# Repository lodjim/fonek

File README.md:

# fonek

Track your own things through Apple's Find My network and see them on your own map, with
hardware you can build yourself.

fonek is three parts that work together:

- **A tag** ([`fonek/`](fonek/README.md)): an open KiCad design for a rechargeable ESP32 BLE
  tag with USB-C charging, plus the [firmware instructions](firmware/README.md) to turn any
  ESP32 dev board into a beacon.
- **A backend** ([`backend/`](backend/)): a FastAPI service that fetches the encrypted
  location reports from Apple with [FindMy.py](https://github.com/malmeloo/FindMy.py),
  decrypts them with the tag's private key and stores them in SQLite. No Mac required.
- **A web app** ([`web/`](web/)): a Next.js + Leaflet dashboard showing each tag's latest
  position and history.

> **Status: prototype.** The software runs today with an ESP32 dev board. The rev A PCB
> passes KiCad ERC/DRC but has not been built and tested yet; see its
> [release checks](fonek/docs/verification.md). fonek is not an Apple-certified Find My
> accessory and relies on an unofficial Apple API.

## How it works

```mermaid
flowchart LR
  TAG["Tag<br>ESP32 + OpenHaystack firmware"] -- "BLE advertisement<br>(public key)" --> PHONE[Nearby iPhones]
  PHONE -- "encrypted location report" --> APPLE[(Apple Find My)]
  APPLE -- "reports for our keys" --> BACKEND["backend<br>FastAPI + FindMy.py"]
  BACKEND --> DB[(data/fonek.db)]
  WEB["web<br>Next.js + Leaflet"] -- "/api" --> BACKEND
```

Each tag has a key pair. The tag broadcasts the public key over Bluetooth. Any iPhone that
passes by encrypts its own location with that key and uploads it to Apple. Only the holder
of the private key can decrypt the report, and that key never leaves your backend.
[docs/architecture.md](docs/architecture.md) goes into the details.

## Quick start

You need Docker, an ESP32 with Bluetooth LE, and an Apple ID with two-factor authentication.
**Use a dedicated Apple ID, not your personal one** (see [Things to know](#things-to-know)).

```bash
git clone https://github.com/lodjim/fonek.git && cd fonek
docker compose up -d --build
docker compose run --rm backend python -m app.cli login   # Apple ID + 2FA, once
```

Then:

1. Open http://localhost:3000 and click **Add device**. fonek generates a key pair and shows
   the advertisement key.
2. Flash that key onto the ESP32, following [firmware/README.md](firmware/README.md).
3. Carry the tag near iPhones. Reports are fetched every 15 minutes, or on demand with
   **Refresh**.

[docs/setup.md](docs/setup.md) covers configuration, backups, updating and troubleshooting.

## Things to know

- **Use a dedicated Apple ID** with 2FA enabled. fonek talks to a private Apple API; an
  account could be rate-limited or locked. Keep the poll interval conservative.
- **Locations are not live.** They arrive only when an iPhone passes near the tag, and
  typically lag by minutes to hours.
- **`data/` holds secrets.** It contains every tag's private key and the Apple session,
  unencrypted. Back it up and keep it private.
- **There is no login on the web app.** Keep it on your LAN and do not expose ports 3000 or
  8000 to the internet.
- **The tag's key is static.** Anyone nearby can recognise the same tag over time.
- **Only track things you own.** Tracking people without their consent is illegal in many
  places and is not what this project is for.

## Repository layout

| Path | What it is |
| --- | --- |
| [`backend/`](backend/) | FastAPI service, poller and CLI (Python 3.11+) |
| [`web/`](web/) | Next.js dashboard |
| [`firmware/`](firmware/README.md) | How to build and flash the OpenHaystack ESP32 firmware |
| [`fonek/`](fonek/README.md) | Rev A tag hardware: KiCad project, Gerbers, BOM, design docs |
| [`docs/`](docs/) | Architecture, setup guide and API reference |
| `docker-compose.yml` | Runs backend and web together |
| `data/` | Created at runtime: database, Apple session (git-ignored) |

## Documentation

- [Architecture](docs/architecture.md): how the pieces fit, the data model, the poller
- [Setup and operation](docs/setup.md): configuration, Apple login, backups, troubleshooting
- [API reference](docs/api.md): the REST endpoints the web app uses
- [Firmware](firmware/README.md): building and flashing the beacon
- [Hardware](fonek/README.md): the rev A tag, its [electrical design](fonek/docs/architecture.md)
  and [verification status](fonek/docs/verification.md)
- [Contributing](CONTRIBUTING.md): development setup and tests

## Development

```bash
# backend
cd backend && python3 -m venv .venv && .venv/bin/pip install -e '.[dev]'
FONEK_DATA_DIR=../data .venv/bin/uvicorn app.main:app --reload
FONEK_DATA_DIR=../data .venv/bin/python -m app.cli seed   # demo device with a fake track
.venv/bin/pytest

# web (proxies /api to http://localhost:8000)
cd web && npm install && npm run dev
```

More in [CONTRIBUTING.md](CONTRIBUTING.md).

## Acknowledgements

fonek stands on other people's work:

- [OpenHaystack](https://github.com/seemoo-lab/openhaystack) by the Secure Mobile Networking
  Lab at TU Darmstadt, which reverse-engineered the Find My protocol and provides the ESP32
  firmware the tag runs.
- [FindMy.py](https://github.com/malmeloo/FindMy.py), which handles the Apple login and
  report decryption.
- Map tiles and data from [OpenStreetMap](https://www.openstreetmap.org/copyright)
  contributors.

fonek is an independent project. It is not affiliated with or endorsed by Apple. Find My and
AirTag are trademarks of Apple Inc.

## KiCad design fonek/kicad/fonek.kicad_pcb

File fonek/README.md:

# fonek — rechargeable BLE finding tag

fonek (Wolof: “where are you?”) is a prototype ESP32 BLE tag for the fonek/OpenHaystack project. Rev A has a protected single-cell LiPo input, USB-C charging, a slide power switch, a green power LED, and a red charging LED. The USB-C port supplies **charging power only**; firmware is flashed through 3.3 V UART test pads.

## Open in KiCad

Open **[`kicad/fonek.kicad_pro`](kicad/fonek.kicad_pro)** in KiCad 9. The editable [schematic](kicad/fonek.kicad_sch), [routed PCB](kicad/fonek.kicad_pcb), project symbol library, and footprint library are all in `kicad/`.

## Order a bare prototype PCB

Upload **[`pcbway/fonek_rev_a_pcbway_bare_pcb.zip`](pcbway/fonek_rev_a_pcbway_bare_pcb.zip)** to a PCB manufacturer such as PCBWay. The ZIP contains front/back copper, masks, silkscreen, board outline, and plated/non-plated drill files. The finished outline is **50 × 50 mm**. Specify **2 layers, 1.0 mm FR-4, 1 oz copper**. The 1.0 mm thickness is required by the selected GCT USB4125 connector's board-edge geometry; do not substitute the usual 1.6 mm thickness without redesigning that connection. Choose a solder-mask color and surface finish per the manufacturer's options.

The ZIP is for **bare board fabrication**. It does not order components, battery, assembly, firmware flashing, or an enclosure. The [`pcbway/assembly/`](pcbway/assembly/) BOM and placement export are preliminary reference files, **not a qualified PCBA order package**. In particular, the protected three-wire LiPo pack with a cell-bonded 10 kΩ NTC still needs a sourced part, mechanical drawing, and polarity check.

KiCad 9 ERC reports **0 errors and 0 warnings**; DRC with schematic parity reports **0 violations and 0 unconnected pads**. See the saved [ERC](reports/erc.rpt), [DRC](reports/drc.rpt), and [fabrication manifest](pcbway/FABRICATION_MANIFEST.txt). These checks validate the file consistency and routing, but physical fit and electrical behavior still need testing on an assembled prototype. The [release checks](docs/verification.md) list what remains before assembled orders or sale.

## Reproduce the fabrication ZIP

From `fonek/`, run `bash scripts/export_pcbway.sh` with `kicad-cli` 9 and Python 3 available. The script re-runs ERC/DRC, exports the fabrication layers and drills, and packages the ZIP only when both reports are clean. The source circuit is [`design/fonek_rev_a.json`](design/fonek_rev_a.json); `python3 scripts/generate.py` refreshes its BOM and readable netlist CSVs, and `python3 -m unittest discover -s tests` checks electrical design invariants. `scripts/generate_board.py` creates a fresh **unrouted** board and will replace the routed PCB, so use it only when intentionally rebuilding the layout.

The [architecture](docs/architecture.md) describes the circuit and its limitations. This is an OpenHaystack prototype, not an Apple Find My certified accessory or an AirTag-equivalent product. It has no UWB precision finding or audible ring. Battery life and RF range are unmeasured.

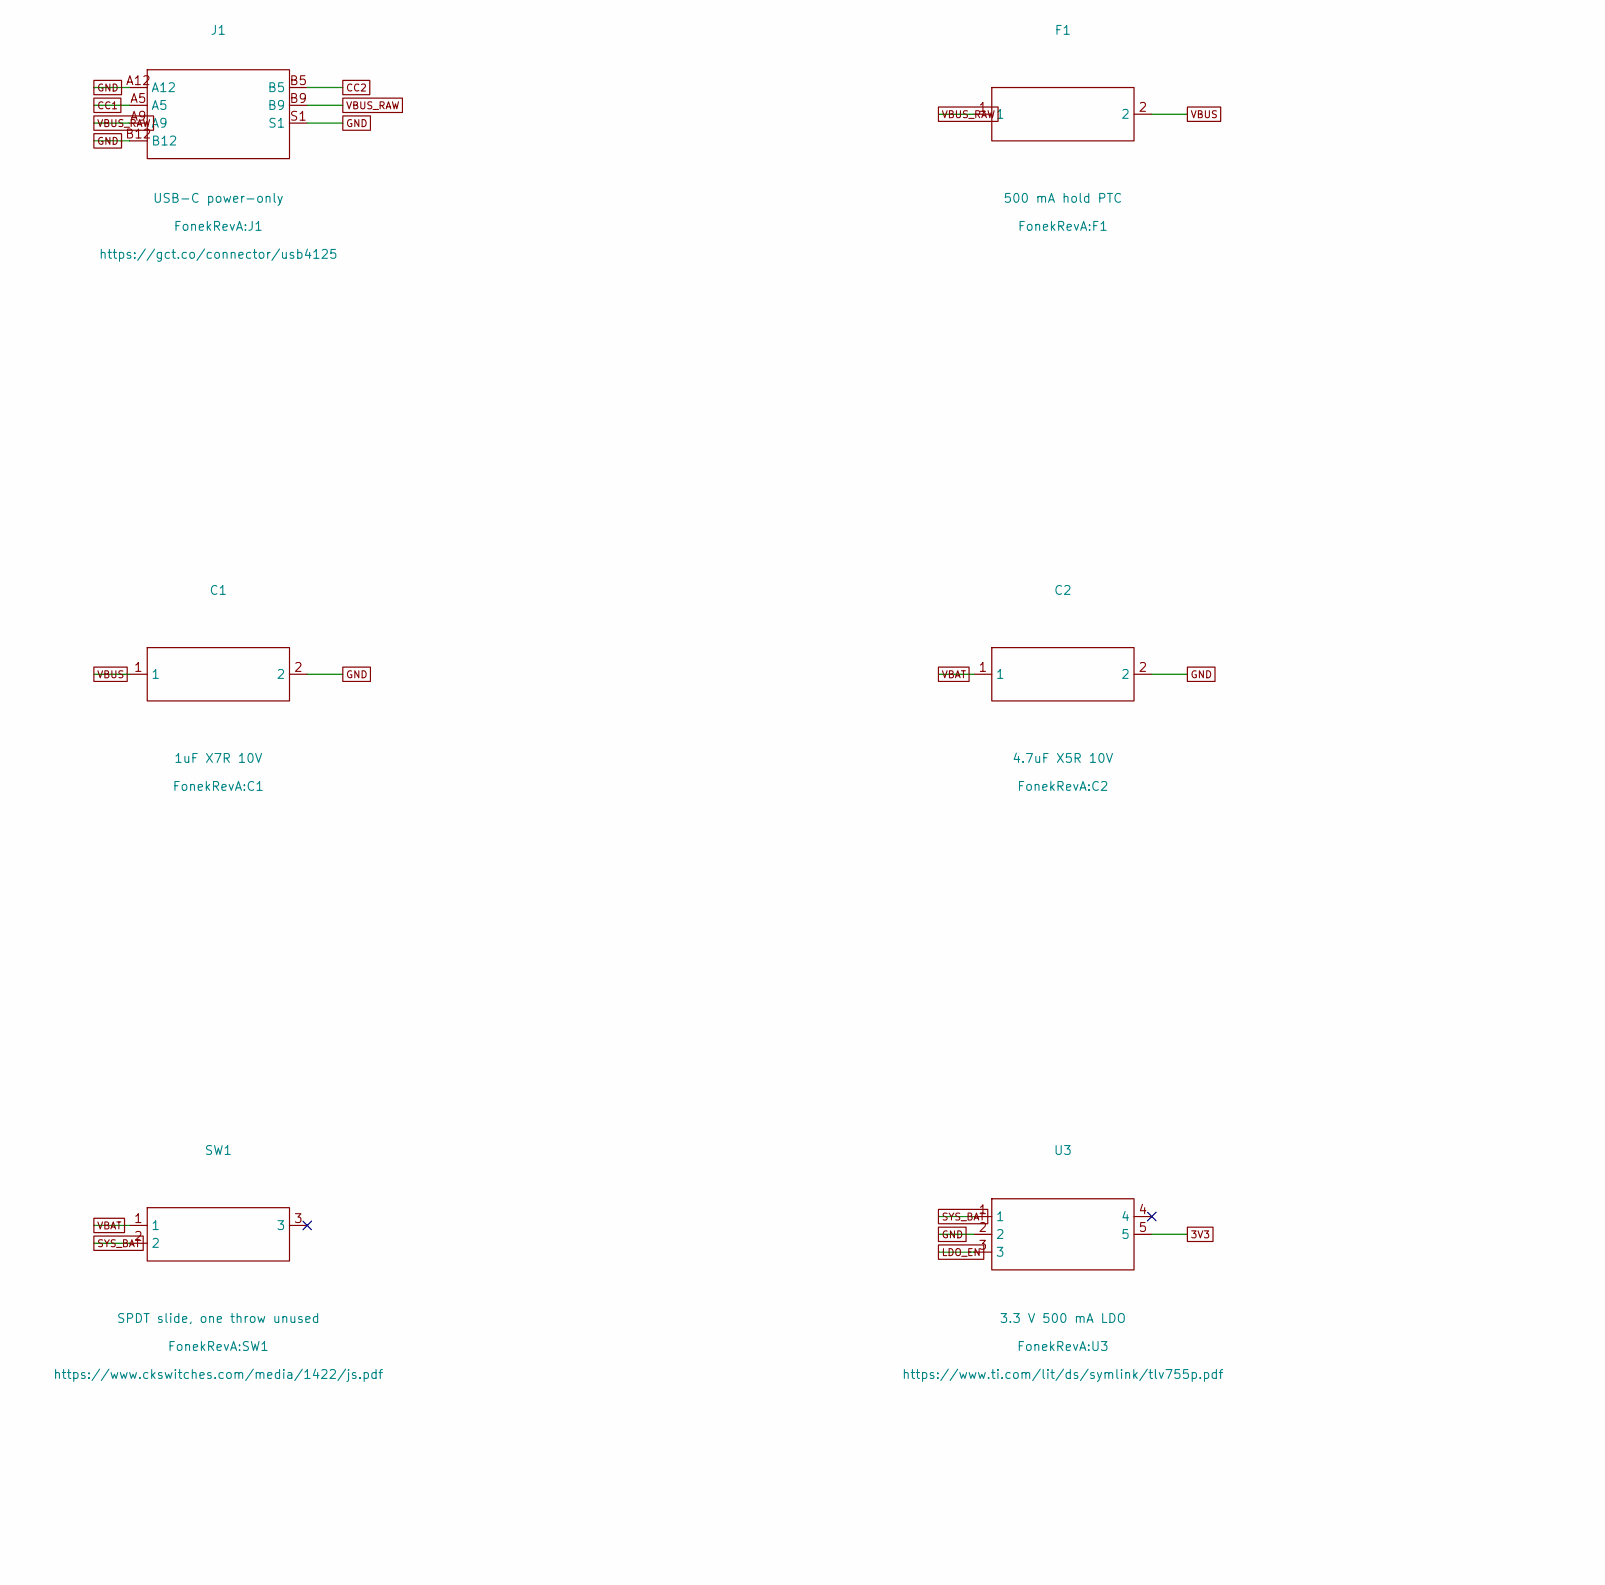
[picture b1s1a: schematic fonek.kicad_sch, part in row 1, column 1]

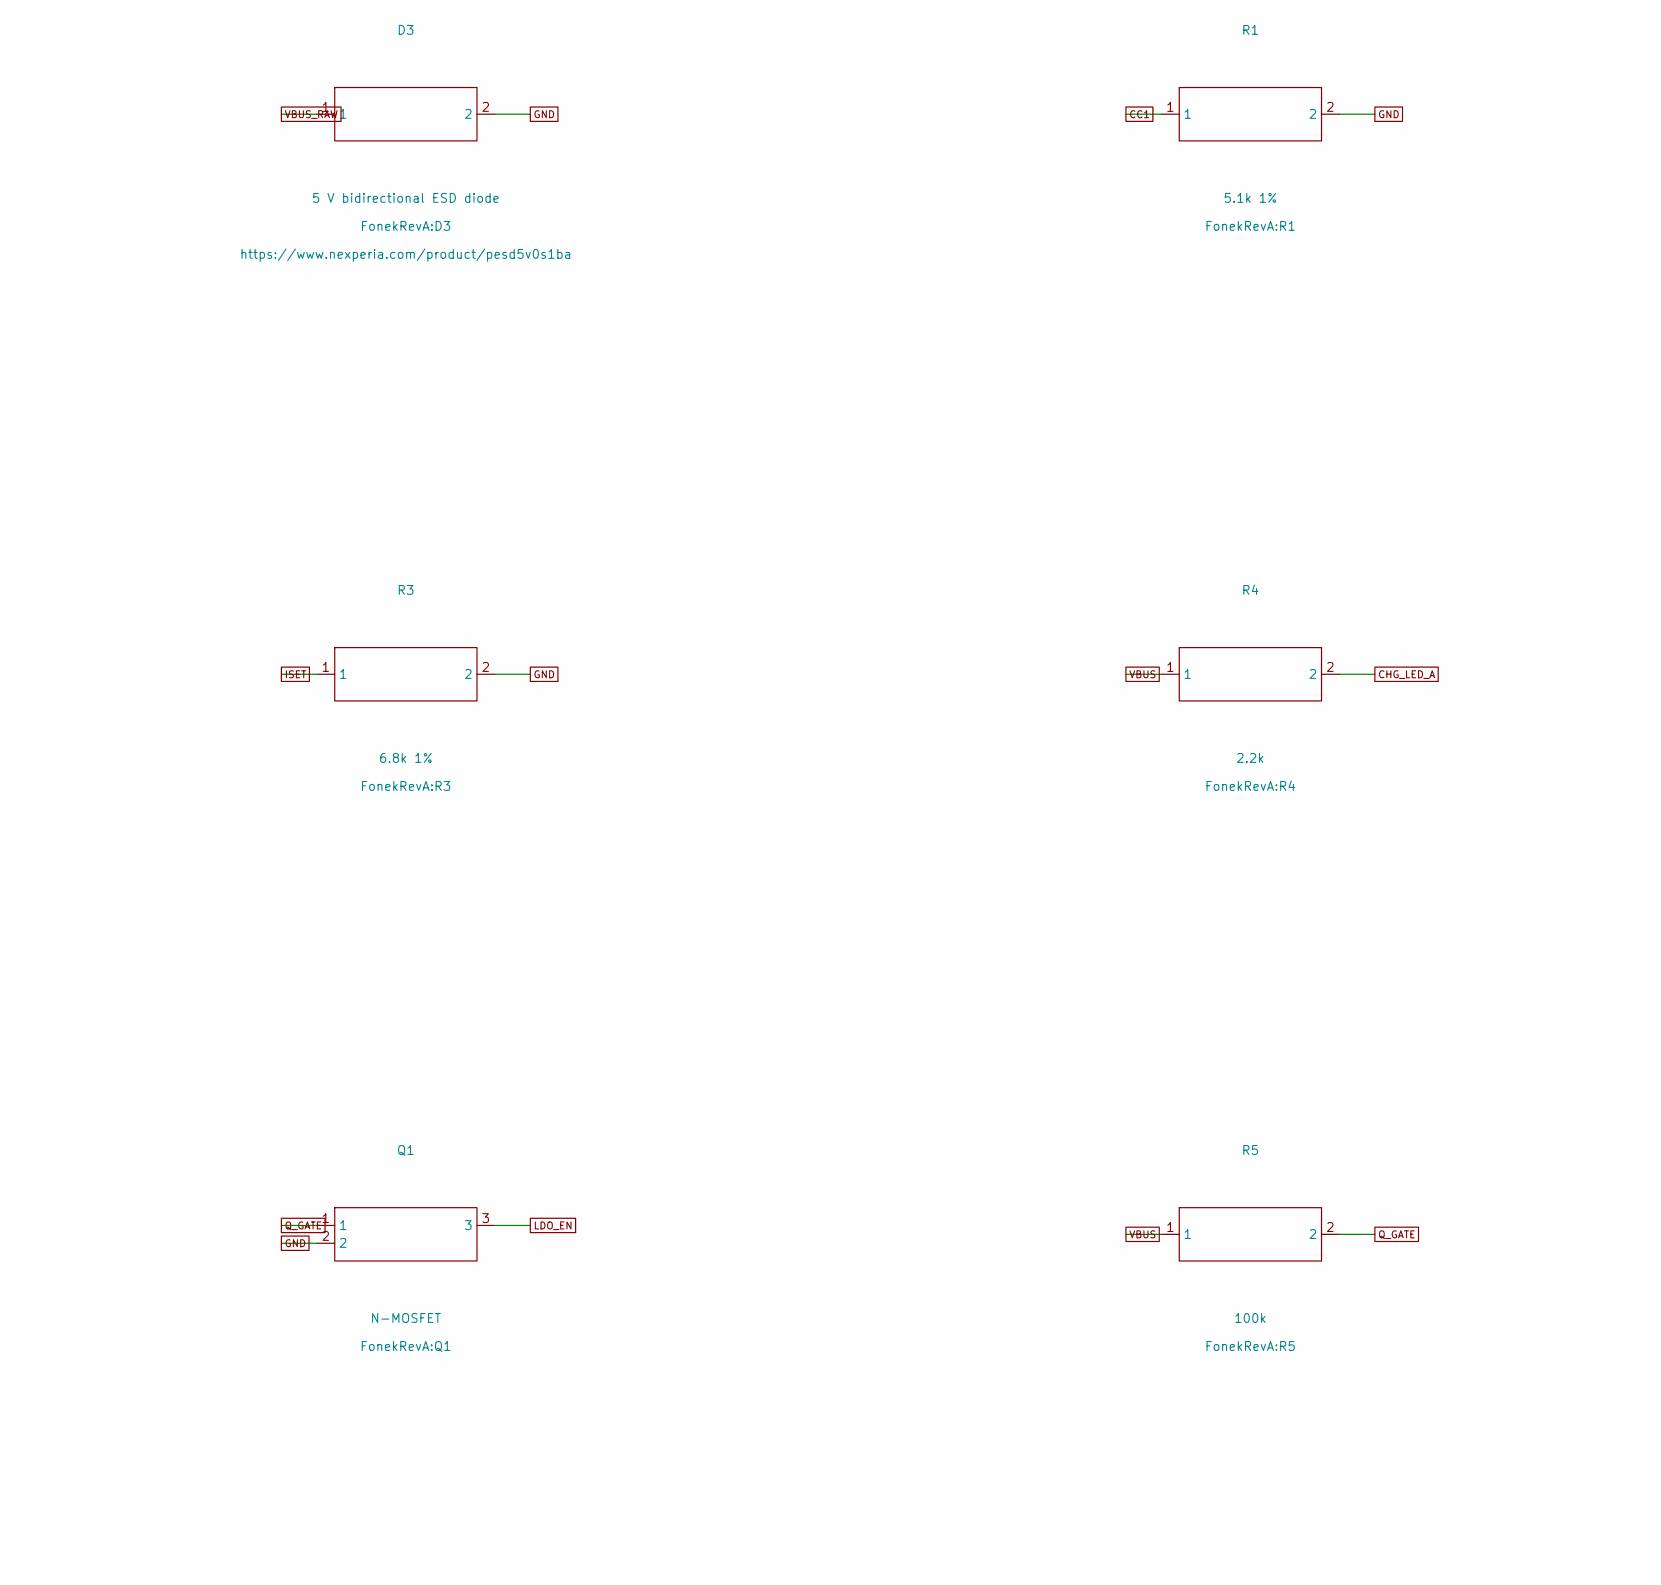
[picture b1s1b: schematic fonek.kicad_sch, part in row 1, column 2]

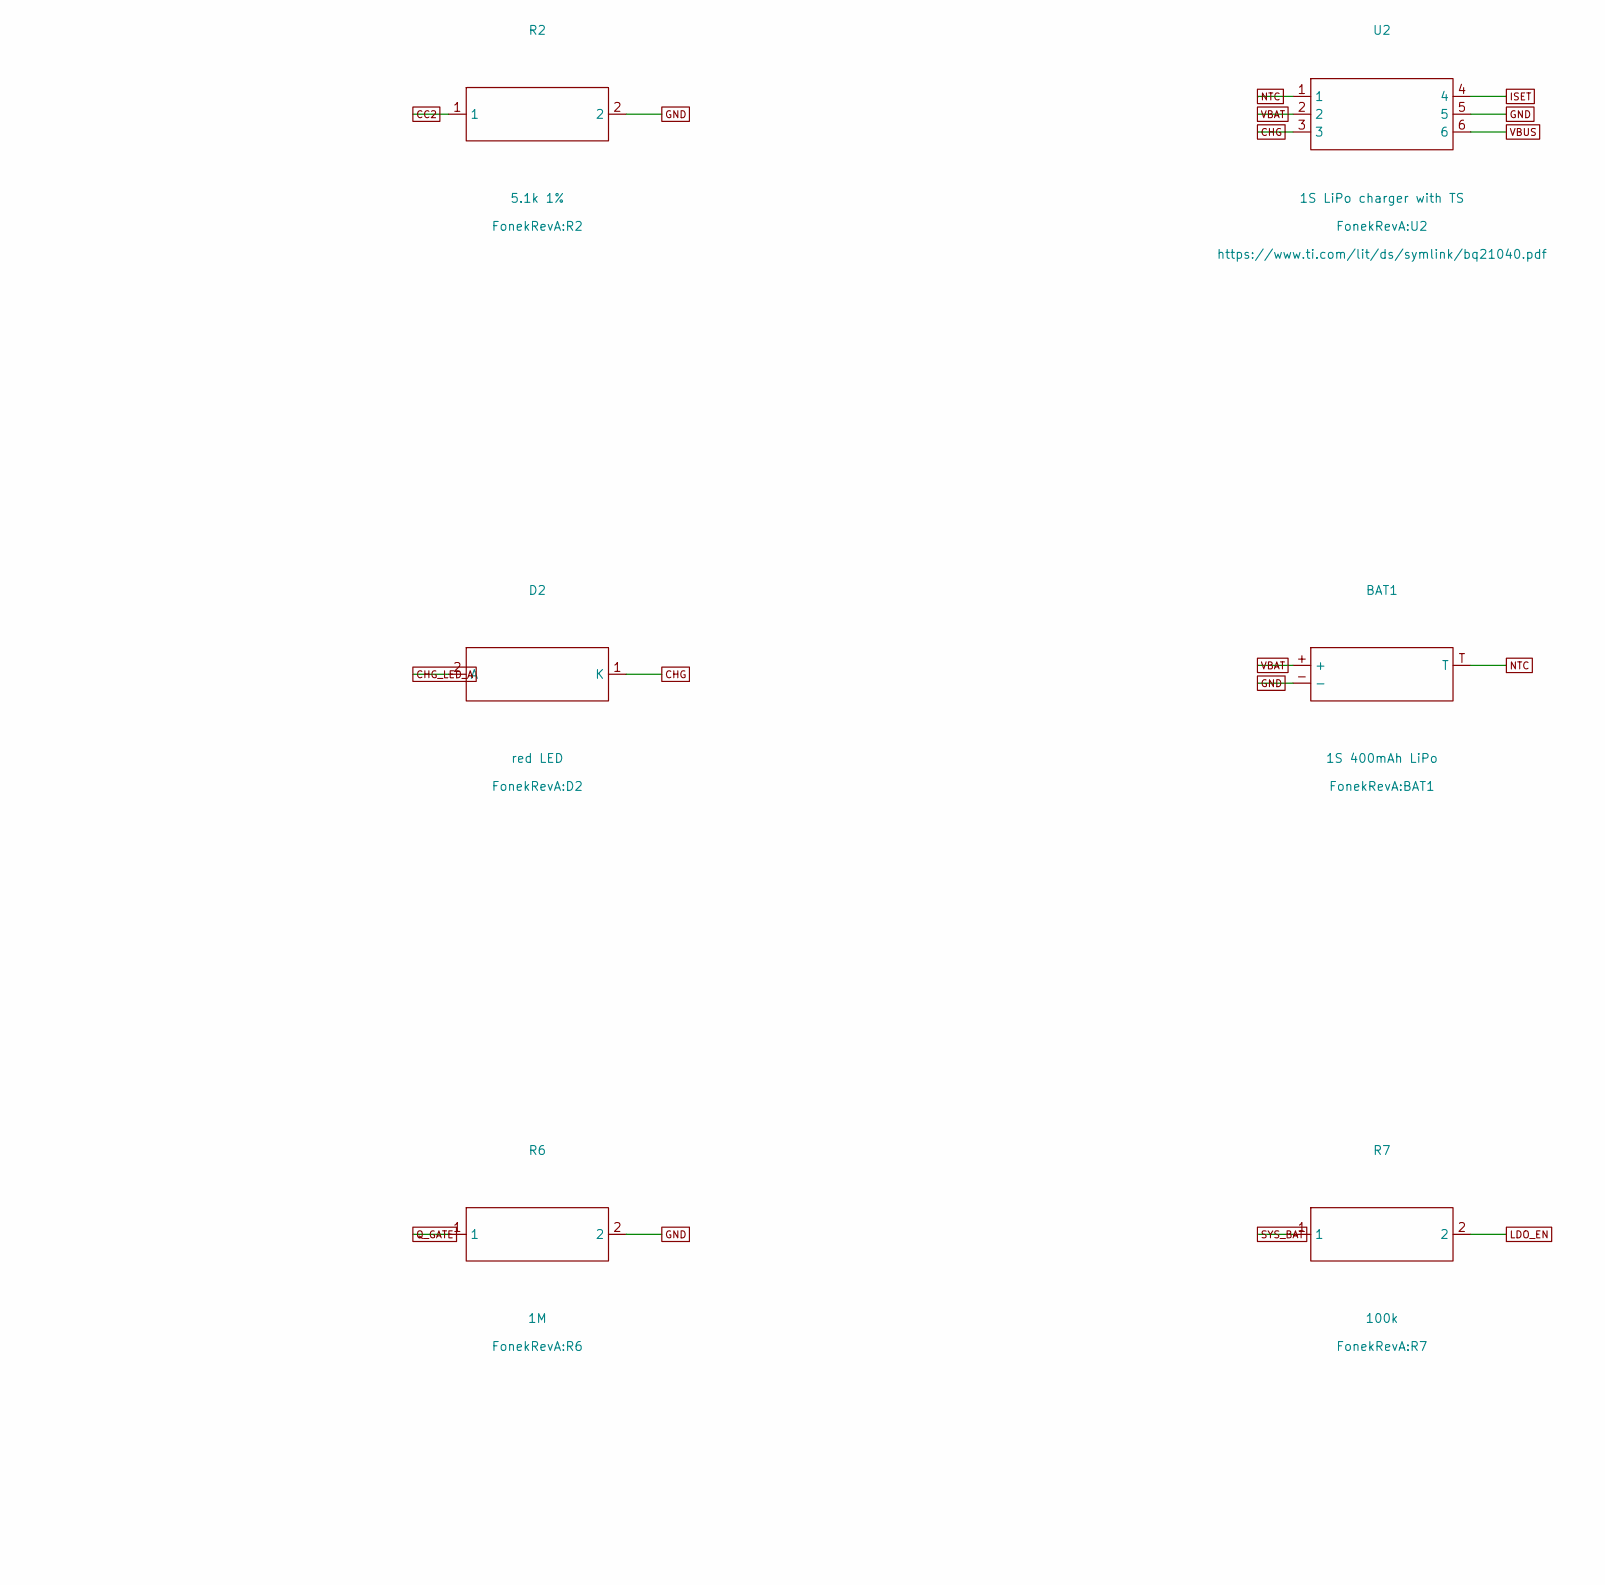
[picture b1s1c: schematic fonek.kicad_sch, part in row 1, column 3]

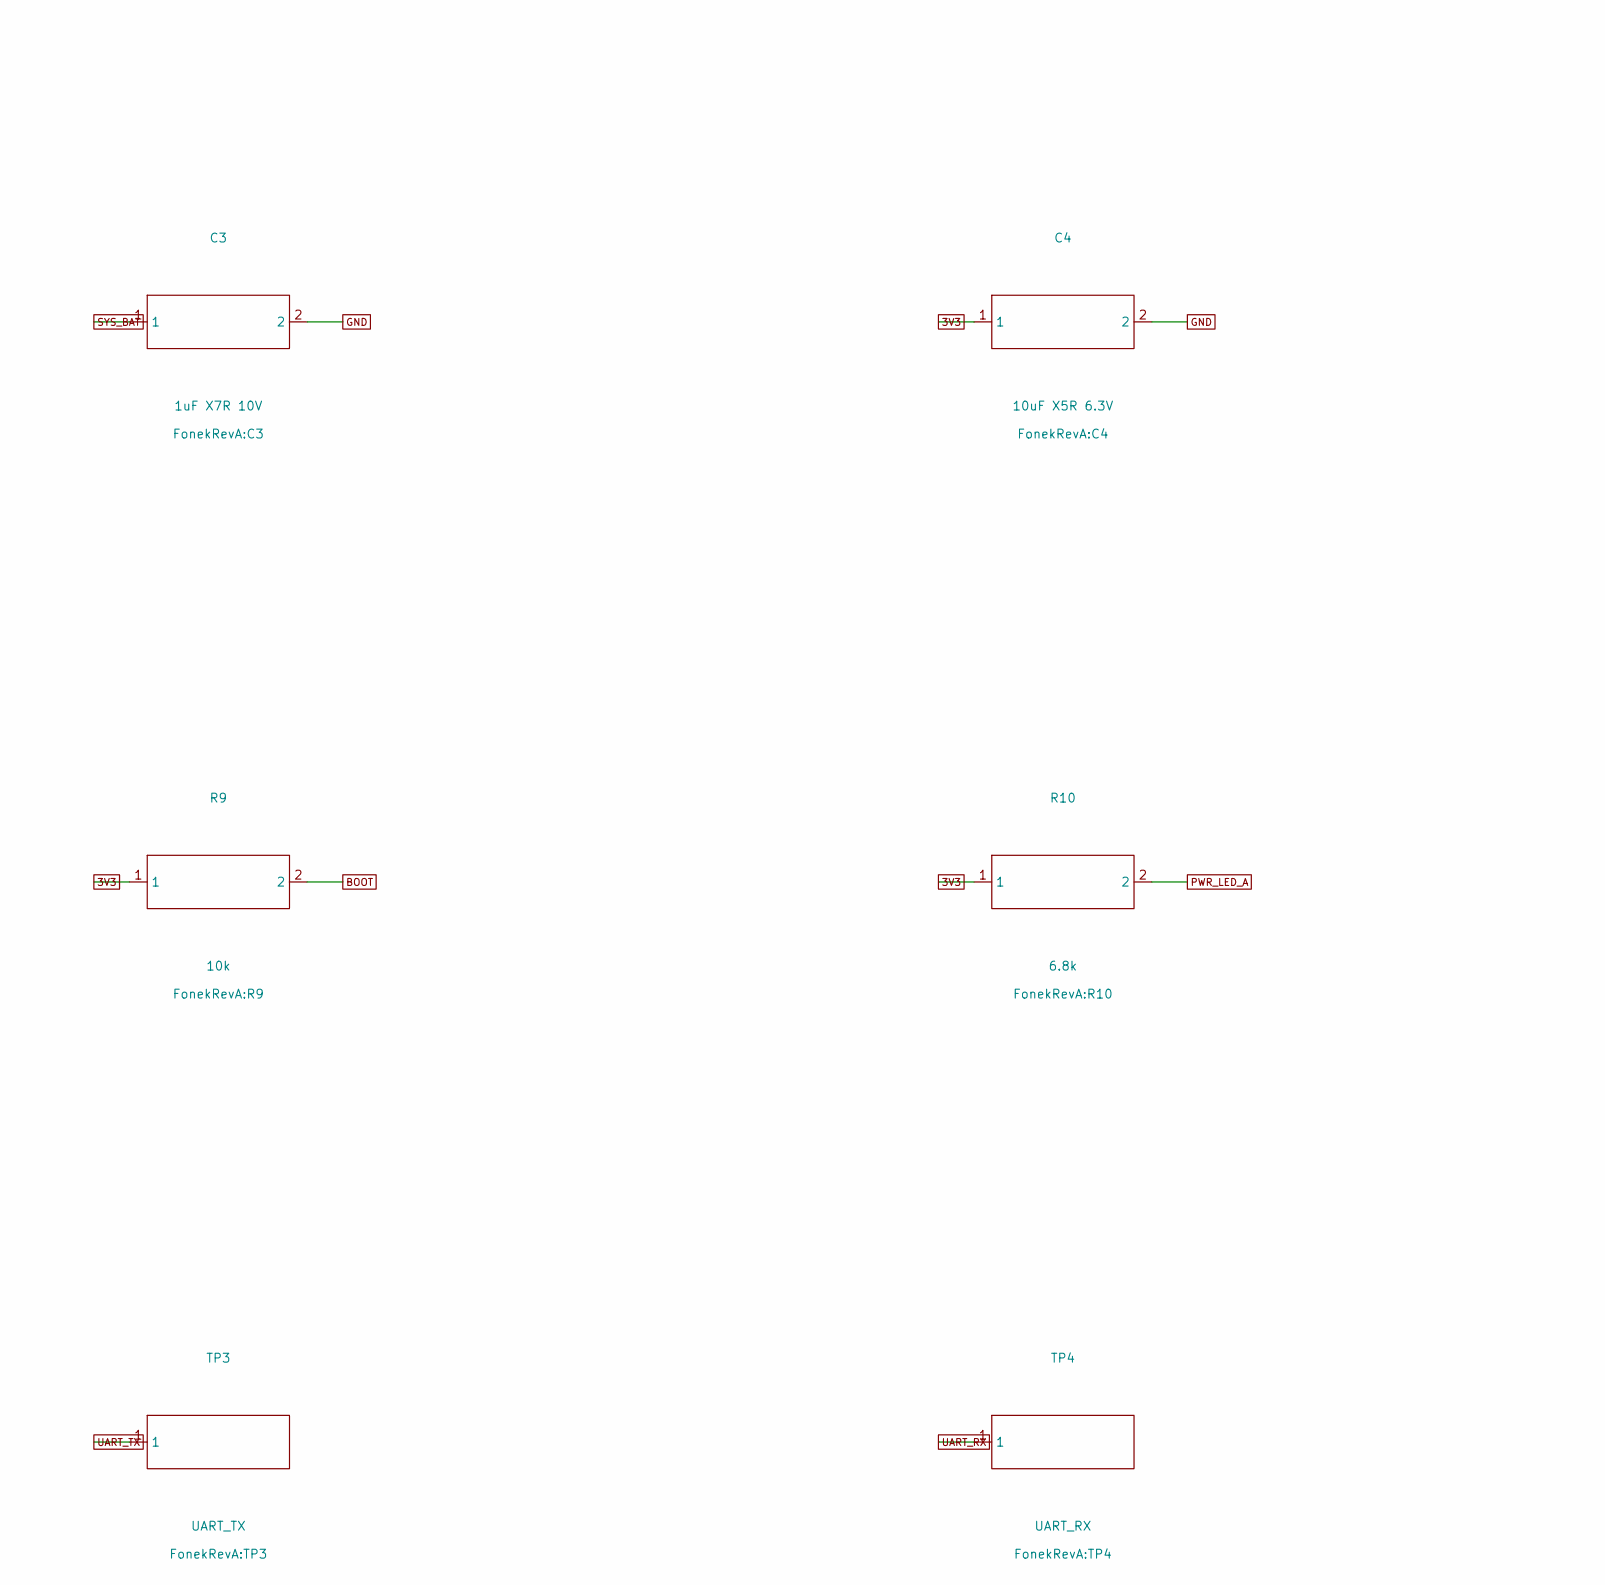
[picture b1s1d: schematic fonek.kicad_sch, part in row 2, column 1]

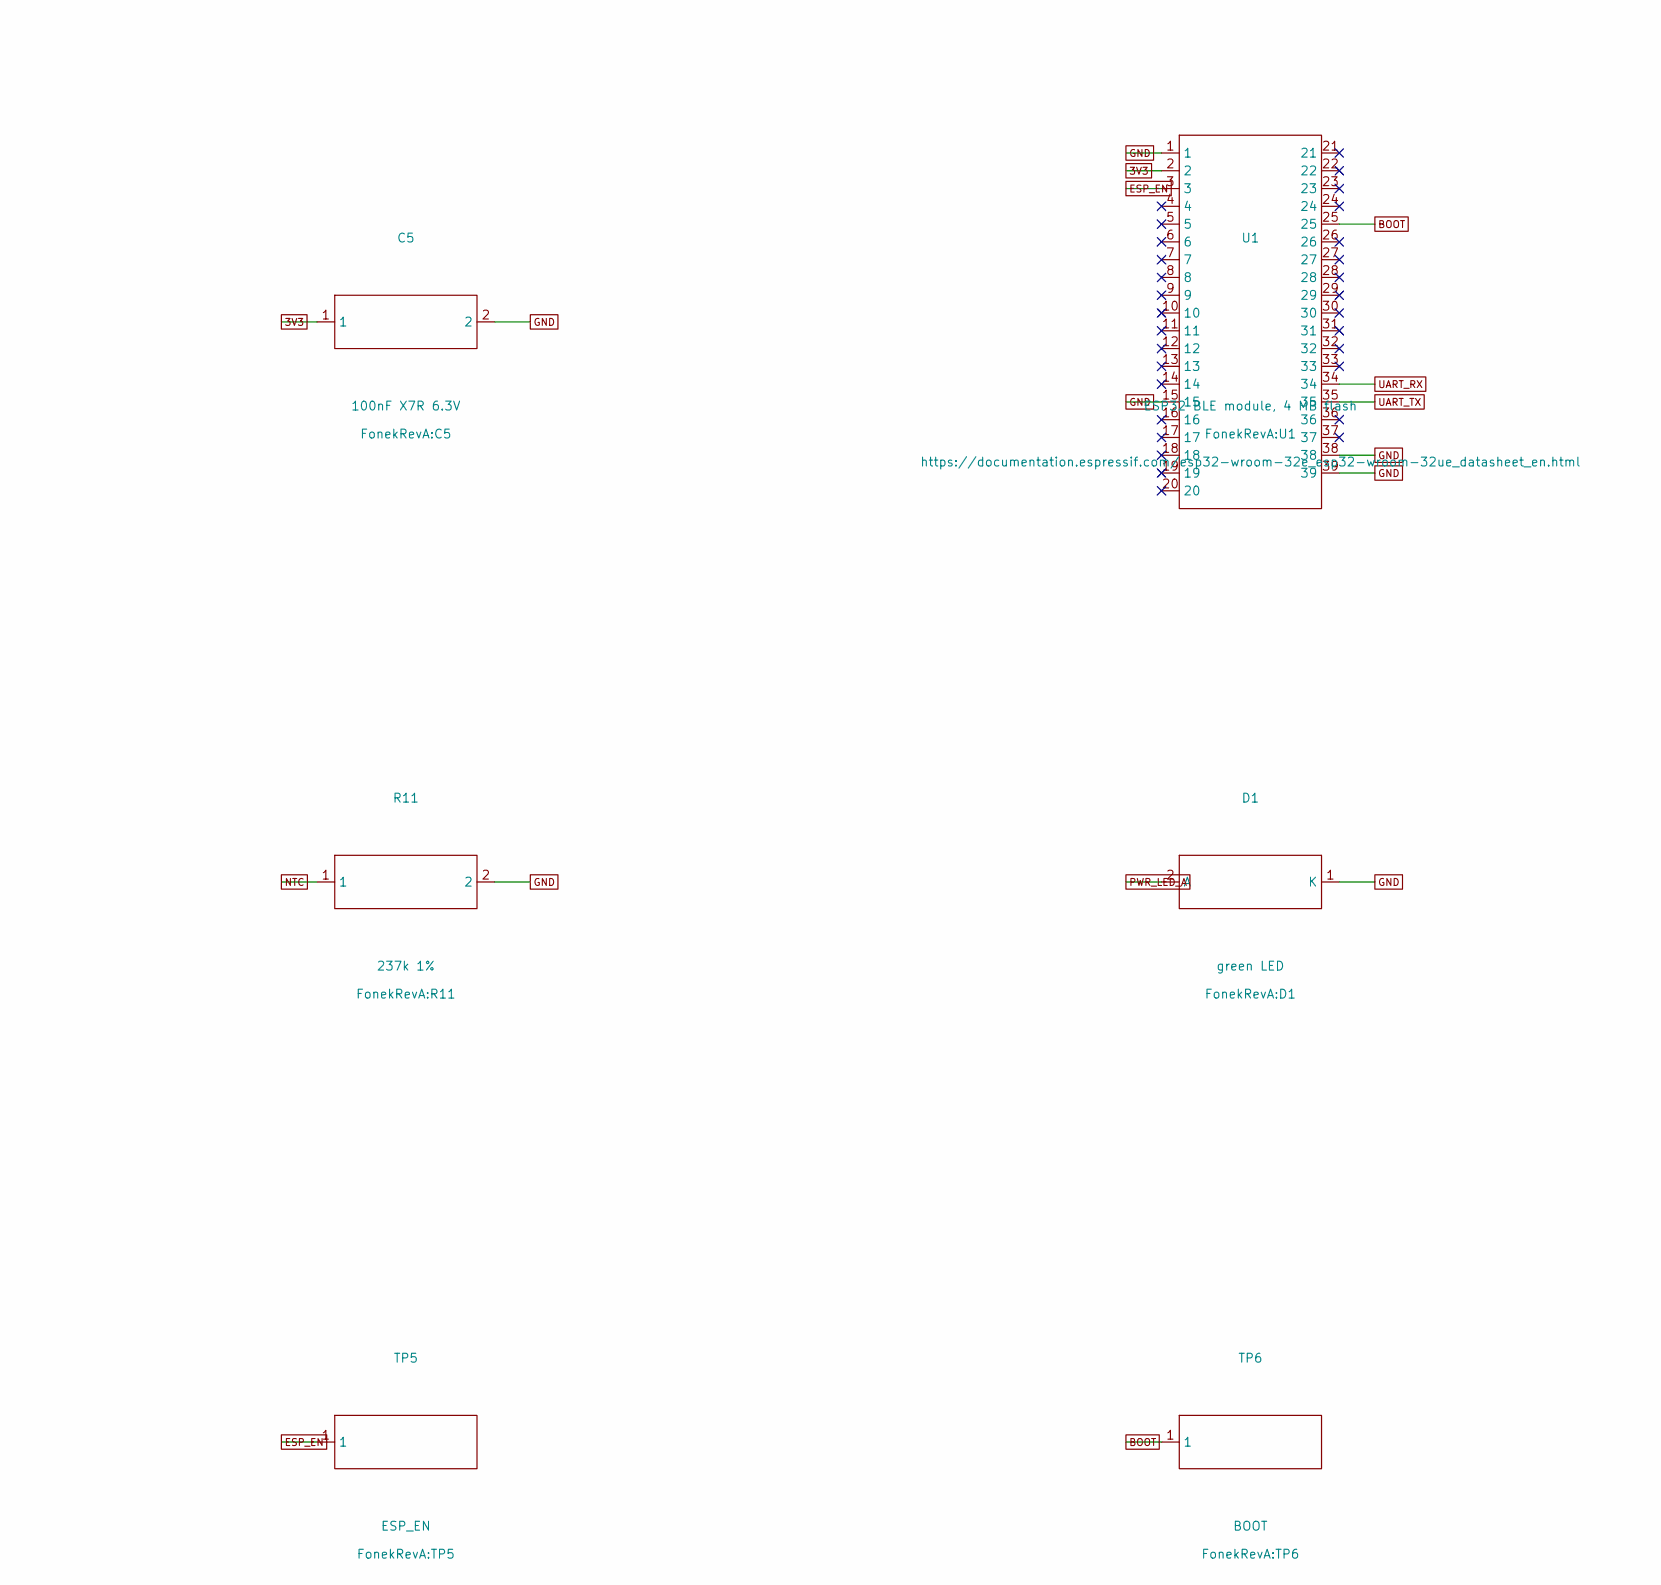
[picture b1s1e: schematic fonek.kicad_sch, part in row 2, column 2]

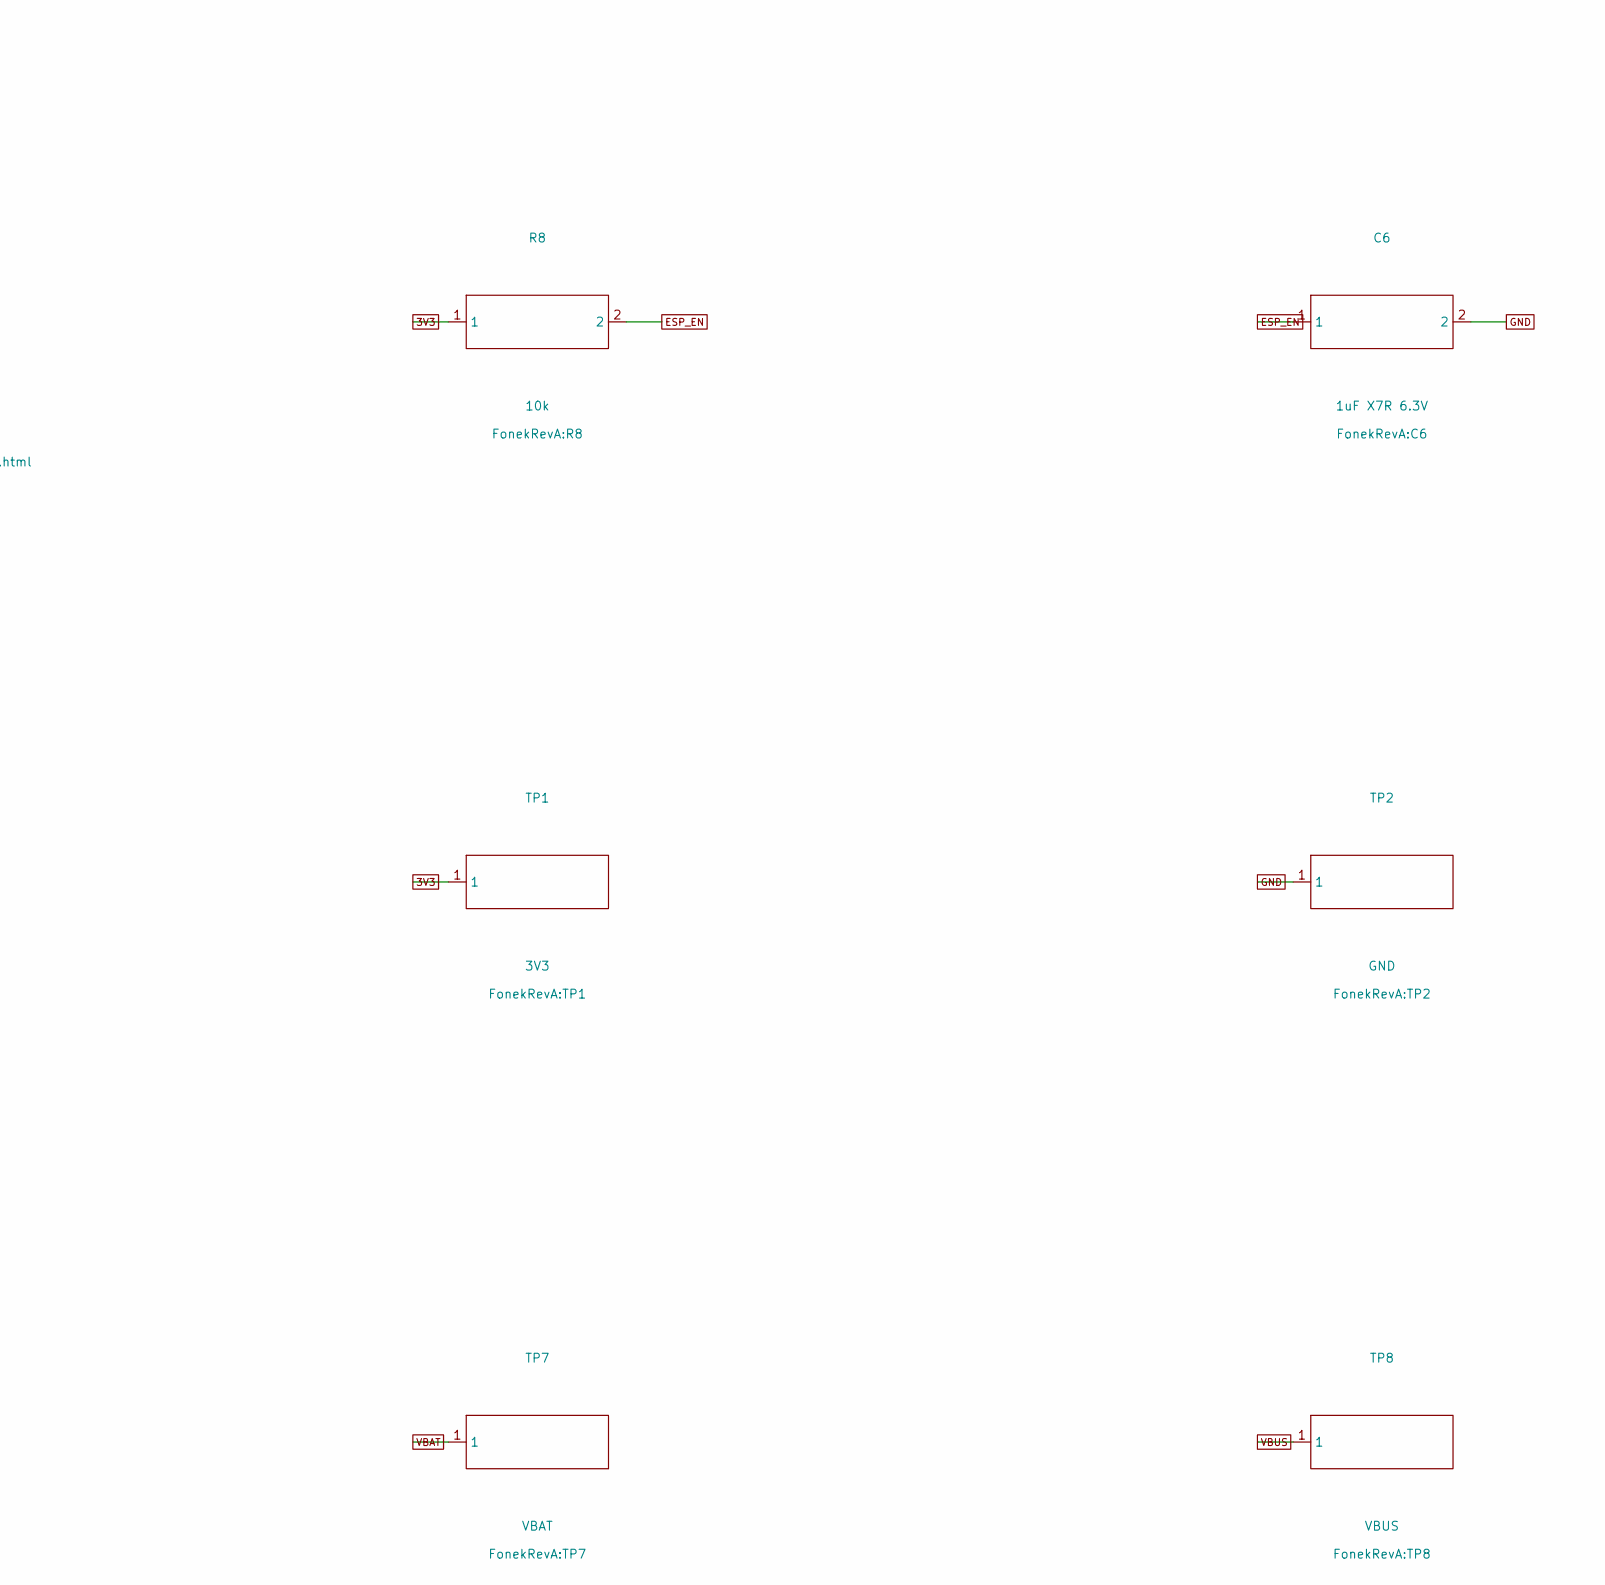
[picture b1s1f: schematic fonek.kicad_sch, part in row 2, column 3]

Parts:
BAT1: 1S 400mAh LiPo; BAT1
C1: 1uF X7R 10V; C1
C2: 4.7uF X5R 10V; C2
C3: 1uF X7R 10V; C3
C4: 10uF X5R 6.3V; C4
C5: 100nF X7R 6.3V; C5
C6: 1uF X7R 6.3V; C6
D1: green LED; D1
D2: red LED; D2
D3: 5 V bidirectional ESD diode; D3
F1: 500 mA hold PTC; F1
J1: USB-C power-only; J1
Q1: N-MOSFET; Q1
R1: 5.1k 1%; R1
R2: 5.1k 1%; R2
R3: 6.8k 1%; R3
R4: 2.2k; R4
R5: 100k; R5
R6: 1M; R6
R7: 100k; R7
R8: 10k; R8
R9: 10k; R9
R10: 6.8k; R10
R11: 237k 1%; R11
SW1: SPDT slide, one throw unused; SW1
TP1: 3V3; TP1
TP2: GND; TP2
TP3: UART_TX; TP3
TP4: UART_RX; TP4
TP5: ESP_EN; TP5
TP6: BOOT; TP6
TP7: VBAT; TP7
TP8: VBUS; TP8
U1: ESP32 BLE module, 4 MB flash; U1
U2: 1S LiPo charger with TS; U2
U3: 3.3 V 500 mA LDO; U3

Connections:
3V3: C4.1, C5.1, R8.1, R9.1, R10.1, TP1.1, U1.2, U3.5
BOOT: R9.2, TP6.1, U1.25
CC1: J1.A5, R1.1
CC2: J1.B5, R2.1
CHG: D2.1 (K), U2.3
CHG_LED_A: D2.2 (A), R4.2
ESP_EN: C6.1, R8.2, TP5.1, U1.3
GND: BAT1.-, C1.2, C2.2, C3.2, C4.2, C5.2, C6.2, D1.1 (K), D3.2, J1.A12, J1.B12, J1.S1, Q1.2, R1.2, R2.2, R3.2, R6.2, R11.2, TP2.1, U1.1, U1.15, U1.38, U1.39, U2.5, U3.2
ISET: R3.1, U2.4
LDO_EN: Q1.3, R7.2, U3.3
NTC: BAT1.T, R11.1, U2.1
PWR_LED_A: D1.2 (A), R10.2
Q_GATE: Q1.1, R5.2, R6.1
SYS_BAT: C3.1, R7.1, SW1.2, U3.1
UART_RX: TP4.1, U1.34
UART_TX: TP3.1, U1.35
VBAT: BAT1.+, C2.1, SW1.1, TP7.1, U2.2
VBUS: C1.1, F1.2, R4.1, R5.1, TP8.1, U2.6
VBUS_RAW: D3.1, F1.1, J1.A9, J1.B9

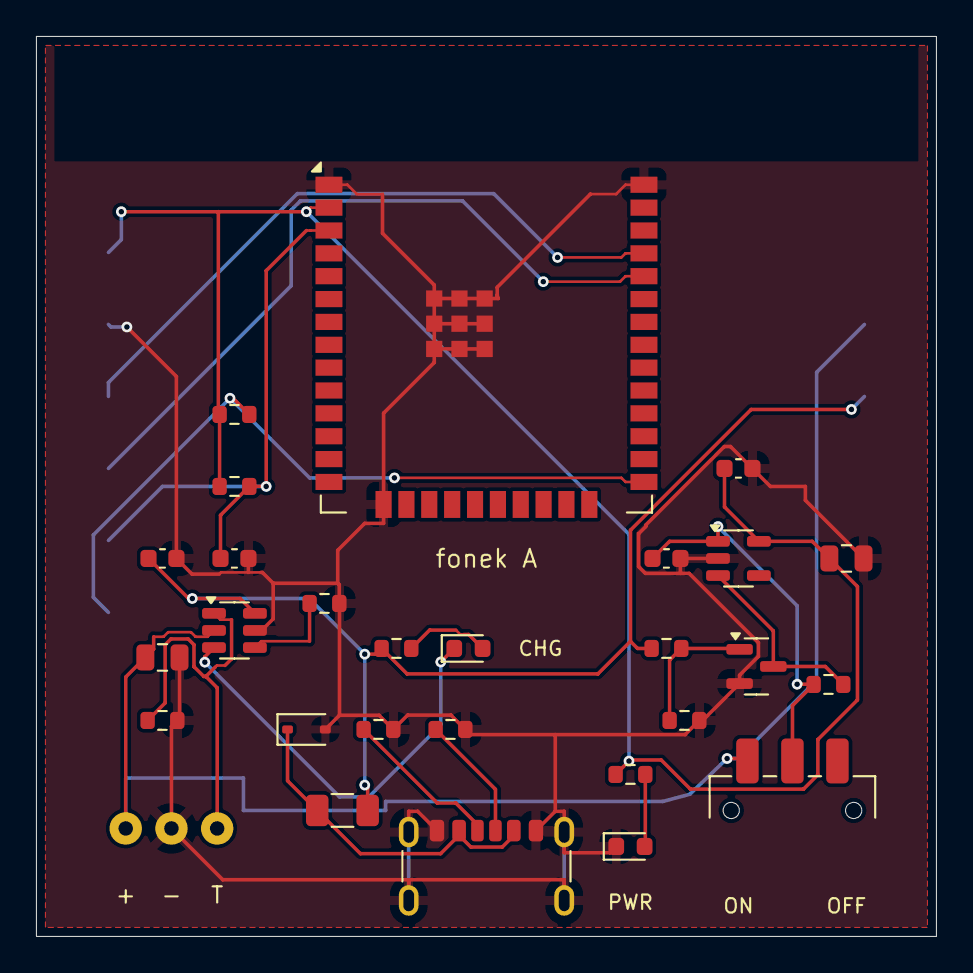
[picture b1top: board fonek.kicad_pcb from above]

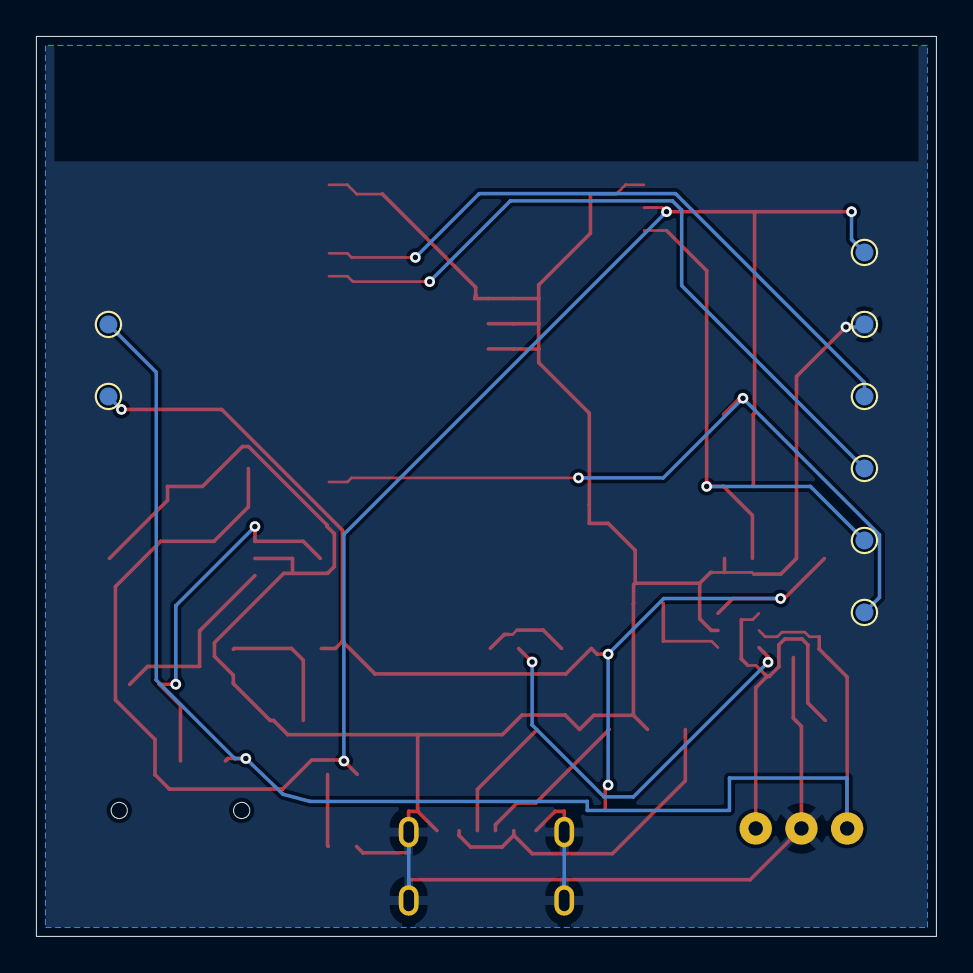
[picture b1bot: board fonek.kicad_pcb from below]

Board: 2 copper layers, 50.0 x 50.0 mm, 36 parts (8 on the bottom side), 19 nets.

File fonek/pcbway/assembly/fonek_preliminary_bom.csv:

ref,part,value,package,role
J1,USB4125-GF-A,USB-C power-only,GCT 6-contact through-hole-shell receptacle,5 V charging port
F1,1206L050/15YR or equivalent,500 mA hold PTC,1206,USB input fault protection
D3,"PESD5V0S1BA,115",5 V bidirectional ESD diode,SOD-323,USB VBUS ESD shunt
R1,generic,5.1k 1%,0603,USB CC1 sink termination
R2,generic,5.1k 1%,0603,USB CC2 sink termination
U2,BQ21040DBVR,1S LiPo charger with TS,SOT-23-6,temperature-qualified charging
C1,generic,1uF X7R 10V,0603,charger input bypass
C2,generic,4.7uF X5R 10V,0805,charger output bypass
R3,generic,6.8k 1%,0603,about 79 mA fast-charge setting
R4,generic,2.2k,0603,charging LED current limit
D2,generic high-efficiency red LED,red LED,0603,on while charging
BAT1,qualified protected 400 mAh pouch pack with 10k NTC lead,1S 400mAh LiPo,27 x 25 x 6 mm target,rechargeable supply; pack sourcing pending
SW1,JS102011SAQN,"SPDT slide, one throw unused",C&K through-hole slide,mechanical ON/OFF
U3,TLV75533PDBVR,3.3 V 500 mA LDO,SOT-23-5,ESP32 supply with enable
Q1,2N7002LT1G,N-MOSFET,SOT-23,turn system off when USB is present
R5,generic,100k,0603,VBUS to MOSFET gate
R6,generic,1M,0603,MOSFET gate pull-down
R7,generic,100k,0603,LDO enable pull-up to switched battery
C3,generic,1uF X7R 10V,0603,LDO input bypass
C4,generic,10uF X5R 6.3V,0805,LDO output bulk capacitor
C5,generic,100nF X7R 6.3V,0603,ESP32 local bypass
U1,ESP32-WROOM-32E-N4,"ESP32 BLE module, 4 MB flash",ESP32-WROOM-32E,BLE location beacon
R8,generic,10k,0603,ESP32 EN pull-up
C6,generic,1uF X7R 6.3V,0603,ESP32 EN power-on delay
R9,generic,10k,0603,GPIO0 boot strap pull-up
R10,generic,6.8k,0603,power LED current limit
R11,generic,237k 1%,0603,prevent TS-open charger timer-disable mode
D1,generic high-efficiency green LED,green LED,0603,on when tracker is powered
TP1,generic,3V3,1 mm test pad,factory programming
TP2,generic,GND,1 mm test pad,factory programming
TP3,generic,UART_TX,1 mm test pad,factory programming
TP4,generic,UART_RX,1 mm test pad,factory programming
TP5,generic,ESP_EN,1 mm test pad,factory programming
TP6,generic,BOOT,1 mm test pad,factory programming
TP7,generic,VBAT,1 mm test pad,battery measurement
TP8,generic,VBUS,1 mm test pad,charge input measurement
